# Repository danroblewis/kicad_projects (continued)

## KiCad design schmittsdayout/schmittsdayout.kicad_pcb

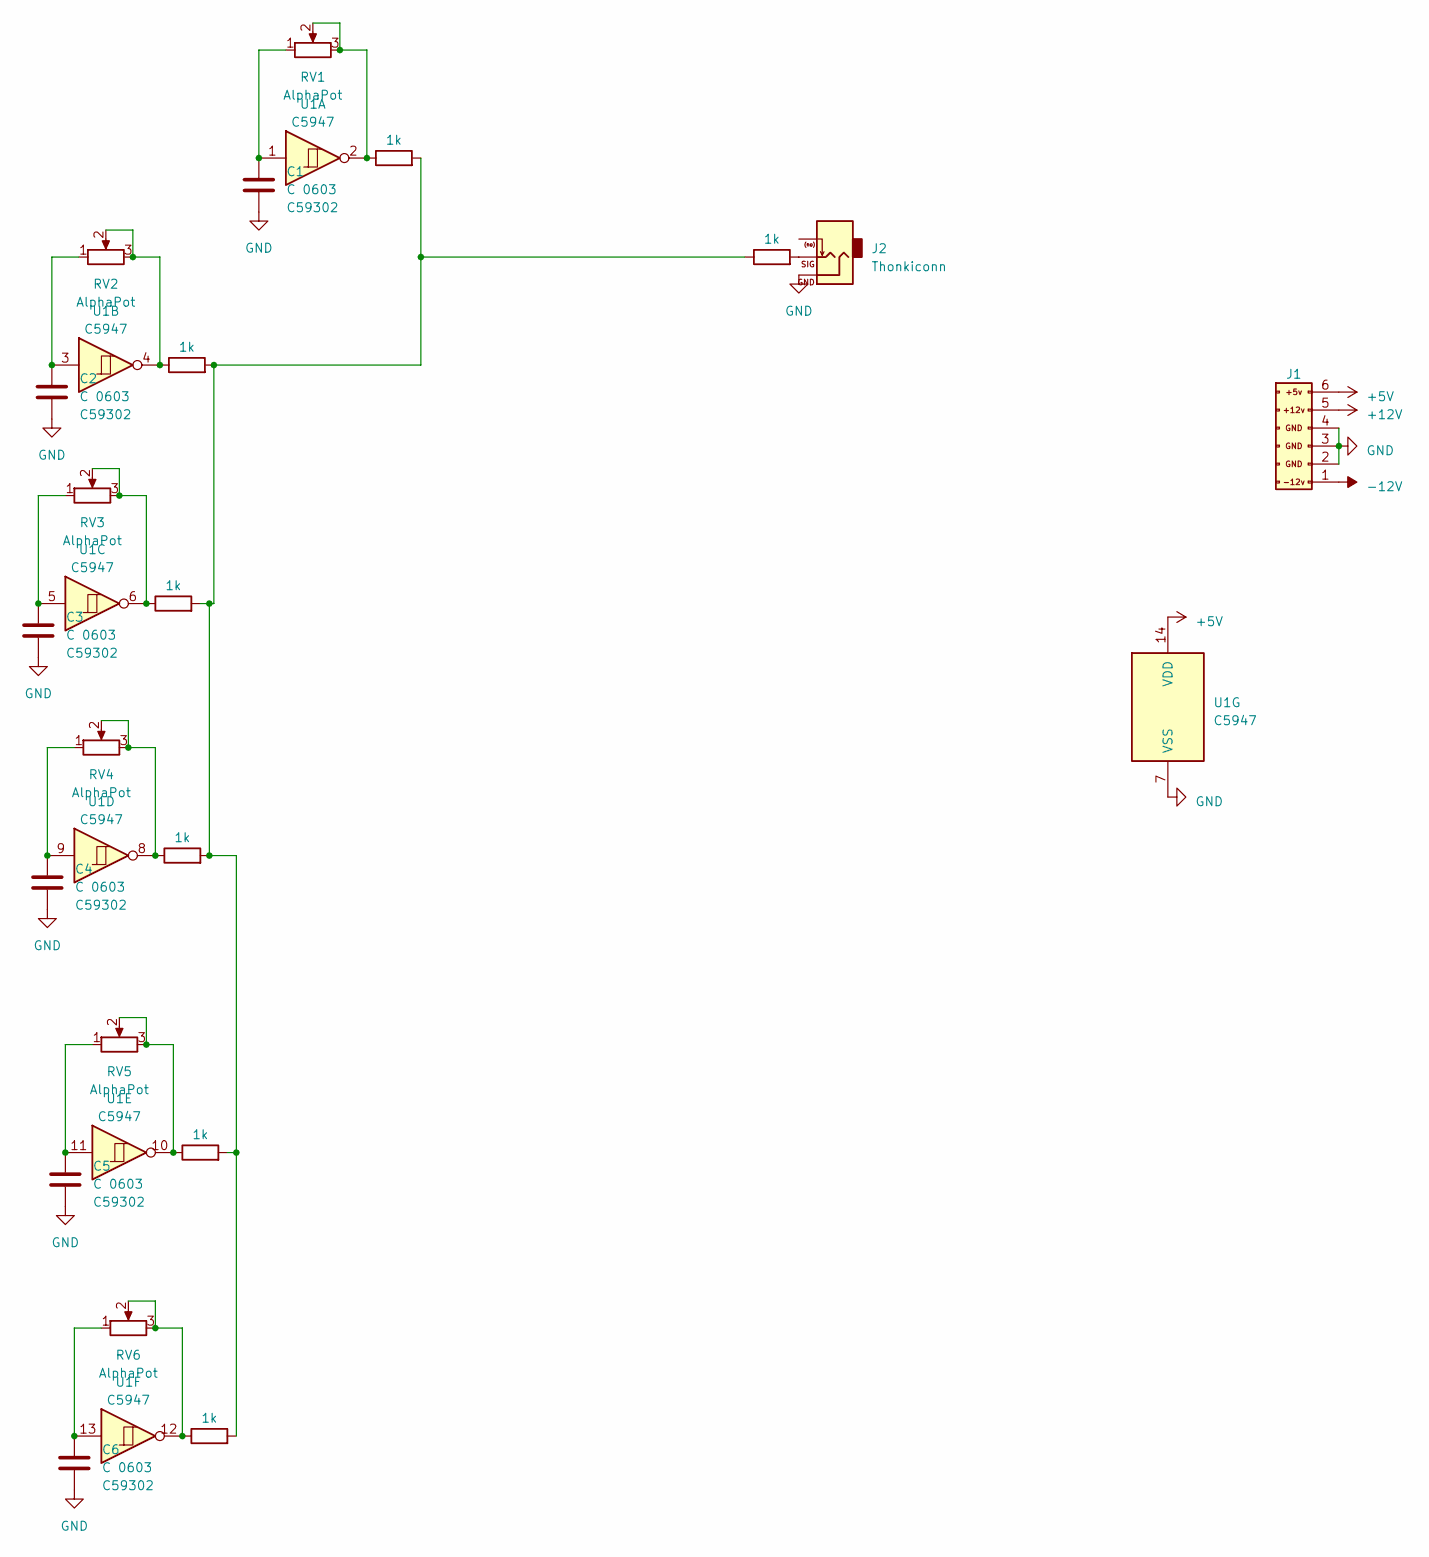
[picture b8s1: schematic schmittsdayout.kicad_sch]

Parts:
C1, C2, C3, C4, C5, C6: C 0603; C_0603_1608Metric; lcsc C59302
J1: EuroPower16; PinHeader_1x07_P2.54mm_Vertical; lcsc C383608
J2: Thonkiconn; Jack_3.5mm_QingPu_WQP-PJ398SM_Vertical_CircularHoles
R1, R2, R3, R4, R5, R6, R7: 1k; R_0603_1608Metric; LCSC C21190
RV1, RV2, RV3, RV4, RV5, RV6: AlphaPot; Potentiometer_Alpha_RD901F-40-00D_Single_Vertical
U1: CD40106; SOIC-16_3.9x9.9mm_P1.27mm; lcsc C5947

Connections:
+5V: J1.6 (GND_L3), U1.14 (VDD)
+12V: J1.5 (GND_R3)
-12V: J1.1 (-12v_R)
GND: C1.1, C2.1, C3.1, C4.1, C5.1, C6.1, J1.2 (-12v_L), J1.3 (GND), J1.4 (GND), J2.S, U1.7 (VSS)
unnamed: C1.2, RV1.1, U1.1
unnamed: C2.2, RV2.1, U1.3
unnamed: C3.2, RV3.1, U1.5
unnamed: C4.2, RV4.1, U1.9
unnamed: C5.2, RV5.1, U1.11
unnamed: C6.2, RV6.1, U1.13
unnamed: J2.T, R7.2
unnamed: R1.1, RV1.2, RV1.3, U1.2
unnamed: R1.2, R2.2, R3.2, R4.2, R5.2, R6.2, R7.1
unnamed: R2.1, RV2.2, RV2.3, U1.4
unnamed: R3.1, RV3.2, RV3.3, U1.6
unnamed: R4.1, RV4.2, RV4.3, U1.8
unnamed: R5.1, RV5.2, RV5.3, U1.10
unnamed: R6.1, RV6.2, RV6.3, U1.12

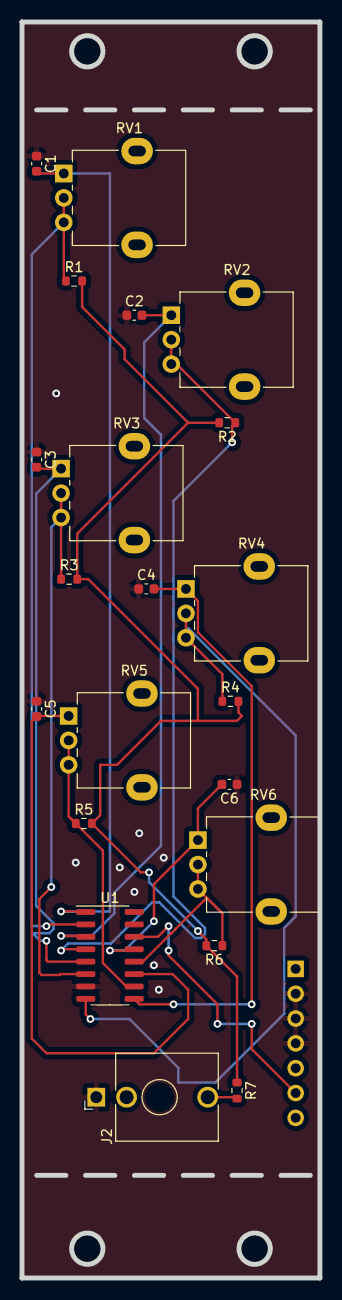
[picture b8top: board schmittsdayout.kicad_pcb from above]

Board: 2 copper layers, 30.5 x 128.5 mm, 22 parts (1 on the bottom side), 16 nets.

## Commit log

2023-03-31 asdf
2023-03-31 qwer
2023-04-14 almost done with wyw v2
